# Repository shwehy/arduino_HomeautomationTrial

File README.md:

# arduino_HomeautomationTrial
some arduino code for a homeautomated project 2015 IEEE protons 15

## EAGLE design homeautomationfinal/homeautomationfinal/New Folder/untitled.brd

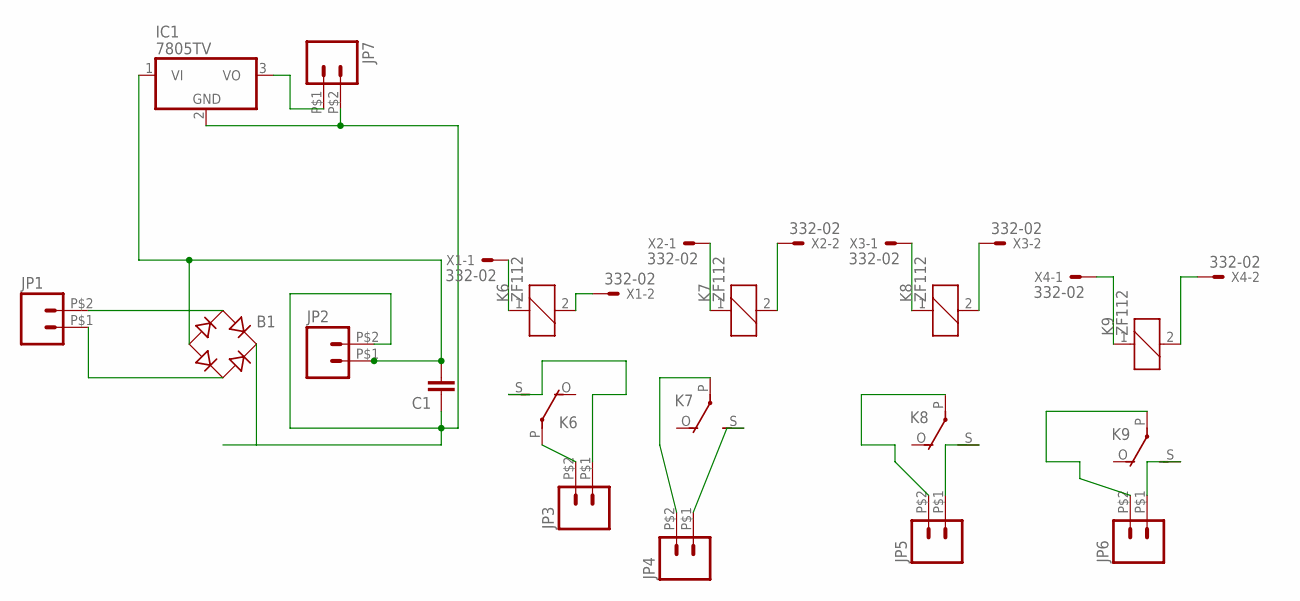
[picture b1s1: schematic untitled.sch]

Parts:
B1: RB1A
C1: CAPKIT; CAP-PTH-SMALL-KIT
IC1: 7805TV; TO220V
JP1, JP2, JP3, JP4, JP5, JP6, JP7: M02PTH2; 1X02_BIG
K6, K7, K8, K9: ZF112
X1, X2, X3, X4: 332-02

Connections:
unnamed: B1.AC1, JP1.P$2 (2)
unnamed: B1.-, C1.2, IC1.1 (VI), JP2.P$1 (1)
unnamed: B1.+, C1.1, IC1.2 (GND), JP2.P$2 (2), JP7.P$2 (2)
unnamed: B1.AC2, JP1.P$1 (1)
unnamed: K6.1, X1.1
unnamed: IC1.3 (VO), JP7.P$1 (1)
unnamed: K6.2, X1.2
unnamed: K7.1, X2.1
unnamed: K7.2, X2.2
unnamed: K8.1, X3.1
unnamed: K8.2, X3.2
unnamed: K9.1, X4.1
unnamed: K9.2, X4.2
unnamed: JP3.P$2 (2), K6.P
unnamed: JP3.P$1 (1), K6.S
unnamed: JP4.P$2 (2), K7.P
unnamed: JP4.P$1 (1), K7.S
unnamed: JP5.P$2 (2), K8.P
unnamed: JP5.P$1 (1), K8.S
unnamed: JP6.P$2 (2), K9.P
unnamed: JP6.P$1 (1), K9.S

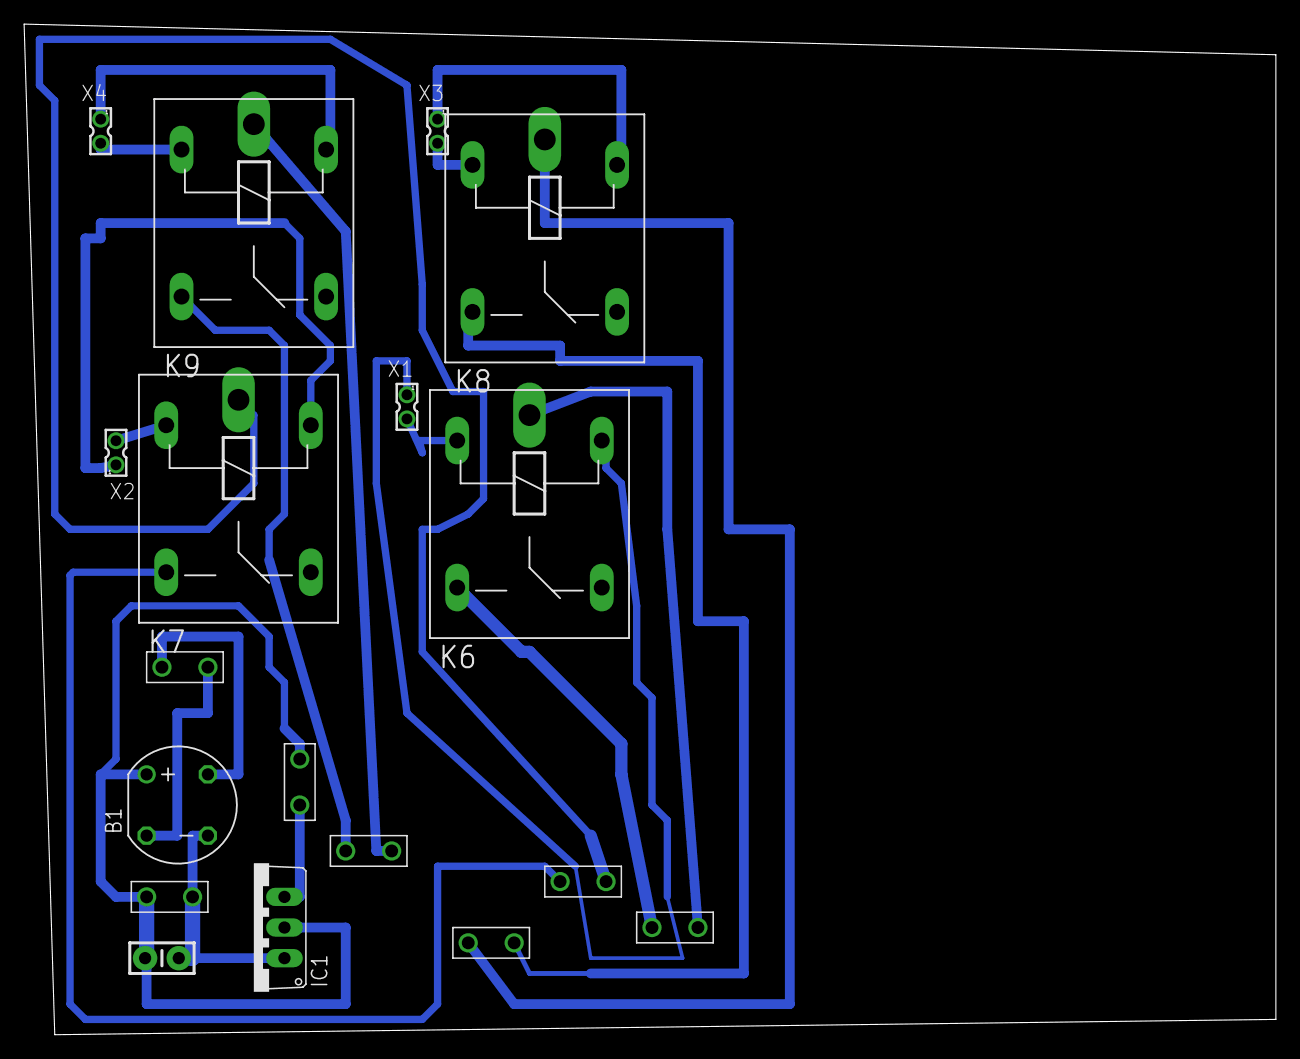
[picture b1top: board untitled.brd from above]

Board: 2 copper layers, 103.8 x 83.8 mm, 18 parts (0 on the bottom side), 21 nets.

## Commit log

2019-10-10 commit1
2019-10-10 rebuild

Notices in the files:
parts and their libraries:
SparkFun-Connectors: Licensing: Creative Commons ShareAlike 4.0 International - https://creativecommons.org/licenses/by-sa/4.0
